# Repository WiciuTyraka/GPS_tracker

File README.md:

# Rocket Localization System

## About

[PUT Rocket Lab](https://tyraka.pl/) jest Kołem Naukowym z Politechniki Poznańskiej zajmującym się projektowaniem, budowaniem oraz testowaniem technologii
rakietowych. Flagowym projektem zespołu jest budowa rakiety sondażowej
Hexa 2 napędzanej hybrydowym silnikiem rakietowym. Jednym z większych problemów, z jakimi przychodzi zmagać się inżynierom budującym
rakiety, jest ich odzysk. Podczas testów rakieta zostaje wystrzelona w
przestrzeń. Wysokość oraz uzyskiwana prędkość obiektu jest oszacowana z
dużą dokładnością. Komplikacje pojawiają się przy estymowaniu miejsca
spadku rakiety, gdyż jest ono zależne w głównej mierze od powodzenia się
wszystkich procedur lądowania oraz w dużym stopniu od czynników meteorologicznych. Istotą odzysku jest zlokalizowanie rakiety w celu znalezienia
części, które są zdatne do ponownego użycia oraz tych, które już nie zadziałają, ale by zanieczyszczały środowisko. Większość zespołów decyduje
się na bardzo drogie komercyjne rozwiązania, które mimo wszystko nie są
wolne od ograniczeń. W tym repozytorium przedstawiony jest autorski projekt systemu lokalizacji rakiet stratosferycznych.

- [Rocket Localization System](#rocket-localization-system)
  - [About](#about)
  - [GPS Tracker](#gps-tracker)
    - [Hardware](#hardware)
      - [Sensors and Components](#sensors-and-components)
      - [Schema](#schema)
      - [Board](#board)
    - [Software](#software)
      - [Block Diagram](#block-diagram)
  - [Receiver](#receiver)
    - [Hardware](#hardware-1)
      - [Sensors and Components](#sensors-and-components-1)
      - [Schema](#schema-1)
      - [Board](#board-1)
    - [Software](#software-1)
      - [Block Diagram](#block-diagram-1)
  - [LoRa Library - RadioTyraka](#lora-library---radiotyraka)
  - [Mobile App](#mobile-app)
    - [Software](#software-1)
  - [App's](#app's)

## GPS Tracker

Pierwszą częścia systemu lokalizacji jest GPS Tracker. Urządzenie to umieszczone wewnątrz rakiety, przy pomocy fal radiowych rozsyła informację na temat swojego aktualnego połorzenia w przestrzeni.

### Hardware

Do komunikacji radiowej ziemia-powietrze posłużyła warstwa fizyczna systemu dalekiego zasięgu - LoRa, protokuł łączności został zaimplementowany według potrzeb naszego zespołu. LoRa używa techniki modulacji z widmem rozproszonym CSS (ang. chirp spread spectrum), która jest uznawana za pierwszą niskokosztową implementację tego rodzaju modulacji do zastosowań komercyjnych. Długość i szerokość geograficzna pozyskiwane są za pomooca systemu nawigacji satelitarnej. Wysokość obliczana jest na podstawie odczytu ciśnienia atmosferycznego mierzonego przez barometr. Z uwagi na stosunkowo niską przepustowość łącza radiowego wszystkie nadmiarowe dane zapisywane sa w trwałej pamięci flash.

Urządzenie jest także wyposażone w akumulator litowo-polimerowy i moduł umożliwiający jego ładowanie przez złącze mini-USB. Cztery diody led pełnią rolę prostego interfejsu, który informuje użytkownika o bierzących ustawieniach. Ustawienia te mogą być konfigurowane poprzez deydkowaną aplikację, która pozwala na ustawienie takich parametrów jak kanał radiowy, moc transmitowanego sygnału oraz data rate. Komunikacja z aplikacją odbywa się poprzez uniwersalny port asynchroniczny - UART. Urządzenie posiada 4 pinowe złącze któe przy pomocy konwertera UART-USB umożliwia podłączenie do komputera. Ostatnim ważnym elementem urządzenia jest włącznik zasilania o logice bistabilnej. Urządzenie zostaje uruchomione poprzez wyciągnięcie specjalnej zworki, tzw "Remove before fly".

<div align="center"><font size="2"><em>Figure 1. Render of GPS Tracker Board</em></font></div>

#### Sensors and components

<details>

Poniższa tabela przedstawia wszytkie moduły cyforwe wykorzystane w projekcie GPS tracker'a wraz z odnośnikiem do poszczególnych dokumentacji.

| Sensor          |          Device |                                                    Datasheet |
| --------------- | --------------: | -----------------------------------------------------------: |
| uC              |      STM32 F411 |              [datasheet](Hardware/datasheet/stm32f411ce.pdf) |
| GPS             |     Quectel L80 | [datasheet](Hardware/datasheet/L80_Hardware_Design_V1.1.pdf) |
| Radio           | LoRa E32-ttl-1W |   [datasheet](Hardware/datasheet/E32-433T30D_Usermanual.pdf) |
| Barometer       |          BMP280 |               [Hardware/datasheet](datasheet/BST-BMP280.pdf) |
| Flash memory    |         W25Q128 |                [Hardware/datasheet](datasheet/w25q128fv.pdf) |
| Battery charger | MCP73833-AMI/UN |             [Hardware/datasheet](datasheet/22005a-76648.pdf) |

</details>

#### Schema

<details>

Poniżej przedstawiony został dokładny schemat GPS tracker'a.

- [link do pliku z schematem](Hardware/gps_tracker2.0/gps_tracker2.0.sch)

<div align="center"><font size="2"><em>Figure 2. Schema of GPS Tracker</em></font></div>

</details>

#### Board

<details>

Na poniższym obrazku przedstawione zostały obie strony dwustronnej płytki PCB, która łączy wszytskie elementy. Lewa strona (niebieskie ścieżki) przedstawia dolną warstwę natomiast prawa (czerwone ścieżki) górną warstwę.

- [link do piku z płytką PCB](Hardware/gps_tracker2.0/gps_tracker2.0.sch)

<div align="center"><font size="2"><em>Figure 3. GPS Tracker board</em></font></div>

</details>

### Software

Napisanie oprogramowania obsługującego moduły urządzenia oraz utworzenie protokołu komunikacyjnego jest niezbędne, by obsłużyć hardware i spełnić wymagania,
które stawiane są przed GPS Tracker'em. W tym celu wykorzystany został popularny framework STM32duino wraz, który jest wygodną i przyjemną platformą do tworzenia aplikacji dla
systemów wbudowanych.
GPS Tracker działa w oparciu o system czasu rzeczywistego FreeRTOS, aby dawać gwarancję wykonania zadań w określonym czasie. Symulacja wielowątkowego działania procesora pozwala
na odczytywanie danych z wszytskich sensorów z maksymalną częstotliwością czujników. Wszystkie dane zapisywane są w trwałej pamięci flash, dzięki czemu po znaleieniu rakiety mogą zostać one odczytane, a na ich podstawie możliwe jest wykreślenie na mapie dokładnego toru lotu rakiety.

Na potrzeby obsługi nowoczesnego modułu komunikacji dalekiego zasięgu -
LoRa - została napisana dedykowana biblioteka. Więcej informacji na jej temat można znaleźć [tutaj](#lora-library---radiotyraka)

#### Block Diagram

<details>

Na pozniższym obrazku przedstawiony został schemat blokowy procesów wykonywanych w ramach działania systemu czasu rzeczywistego zaimplementowanego na potrzeby obługi GPS Tracker'a.

- [link do pliku z kodem źródłowym GPS Tracker'a](Software/gps_tracker/transmiterRTOS_ConfigRadioTyraka.ino)

<div align="center"><font size="2"> <em>Figure 4. GPS Tracker code diagram</em></font></div>

</details>

## Receiver

Drugą częścią systemu jest Receiver, który wraz z smartfonem tworzy stację odbiorczą dla sygnału emitowanego z rakiety. Urządzenie wyposażone w antenę kierunkową pozwala na łączność z rakietami odbywającymi loty stratosferyczne. Odebrane dane wizualizowane są w czasie rzeczywistym na mapie satelitarnej na ekranie połączonego smartfona.

### Hardware

Receiver jest stosunkowo prostym urządzeniem, wyposażoy jest oczywiście w odbiornik radiowy umożliwiający nawiązenie komunikaji radiowej z rakietą oraz jego działanie oparte jest o mikrokontroler ESP32, który posiada zintegrowany moduł Bluetooth i Wi-Fi. Urządzenie wyposażone jest także w 4 złącza umożliwiające komunikację przewodową poprzez różne protokoły, takie jak 2x UART, SPI, I2C. Zastosowanie tak mnogiej liczby interfejsów sprawia, że receiver jest bardzo uniwersalnym urządzeniem, które może zostać w łatwy i przyjemny sposób wykorzystane w wielu projektach jako gateway dla sygnału radiowego LoRa.

Na potrzeby naszego systemu wykorzystywane są trzy interfejsy. Przy pomocy standardu bezprzewodowego Bluetooth Receiver łączy się z smartfonem który przy pomocy dedykowanej aplikacji staje wyświetlaczem dla danych telemetrycznych odbieranych z rakiety.
standard komunikacji Wi-Fi, wykorzystywany jest do postowania odebranych danych na server za pomocą rest api.
Użytkownik ma dostęp do nich poprzez naszą aplikację, która archiwizuje i umożliwia przeglądanie wszystkich danych z różnych lotów i testów.
Ostatnim wykorzystanym interfejsem jest UART, podpobnie jak w przypadku GPS Tracker'a służy on do konfigurowania parametrówtransmisji takich jak kanał radiowy, moc transmitowanego sygnału oraz data rate.

<div align="center"><font size="2"><em>Figure 1. Render of Receiver Board</em></font></div>

#### Sensors and components

<details>

Poniższa tabela przedstawia wszytkie moduły cyforwe wykorzystane w projekcie GPS tracker'a wraz z odnośnikiem do poszczególnych dokumentacji.

| Sensor |          Device |                                                  Datasheet |
| ------ | --------------: | ---------------------------------------------------------: |
| uC     |           ESP32 |        [datasheet](Hardware/datasheet/esp32_datasheet.pdf) |
| Radio  | LoRa E32-ttl-1W | [datasheet](Hardware/datasheet/E32-433T30D_Usermanual.pdf) |

</details>

#### Schema

<details>

Poniżej przedstawiony został dokładny schemat Receivera.

- [link do pliku z schematem](Hardware/receiver/receiver.sch)

<div align="center"><font size="2"><em>Figure 5. Schema of Receiver</em></font></div>

</details>

#### Board

<details>

Na poniższym obrazku przedstawione zostały obie strony dwustronnej płytki PCB, która łączy wszytskie elementy. Lewa strona (niebieskie ścieżki) przedstawia dolną warstwę natomiast prawa (czerwone ścieżki) górną warstwę.

- [link do piku z płytką PCB](Hardware/receiver/receiver.brd)

<div align="center"><font size="2"><em>Figure 6. Receiver board</em></font></div>

</details>

### Software

Podobnie jak w przypadku GPS Tracker'a kod został napisany z wykorzystaniem freamworku Arduino. Jednak w tym przypadku system czasu rzeczywistego nie został wykorzystany, kod działa w sposób proceduralny.
Do obsługi modułu komunikacji radiowej, również została wykorzystana autorska biblioteka.

#### Block Diagram

<details>

Na pozniższym obrazku przedstawiony został schemat blokowy proceduralnego kodu Receiver'a

- [link do pliku z kodem źródłowym Receiver'a](Software/receiver/eciverRadioTyrakaV2.ino)

<div align="center"><font size="2"> <em>Figure 7. Receiver code diagram</em></font></div>

</details>

## LoRa Library - RadioTyraka

Na potrzeby obsługi nowoczesnego modułu komunikacji dalekiego zasięgu -
LoRa - została napisana dedykowana biblioteka. Biblioteka implementuje protokuł komunkacyjny, który znacząco ułatwia komunikację radiową natomiast obsługa modułu jest przyjamna dla użytkownika. Wydajność łącza radiowego uzyskana dzięki oprogramowaniu naszego zespołu jest większa niż w przypadku użytkowania biblioteki afirmowanej przez producenta modułu.

RadioTyraka powstało jako nakładka na popularną bibliotekę [RadioHead](https://www.airspayce.com/mikem/arduino/RadioHead/). Znacząco usprawnia ona niektóre z funkcji oferowanych przez bibliotekę, a także wprowadza nowe użyteczne rozwiązania. Biblioteka RadioTyraka znajduje się na osobnym repozytorium, które zawiera jej szczegółową dokumentację.

- [link do repozytorium z biblioteką](https://github.com/WiciuTyraka/RadioTyraka)

## Mobile App

W celu wizualizacji lokalizacji szukanego obiektu stworzona została aplikacja mobilna. Aplikacja łączy się za pomocą technologii Bluetooth ze
stacją odbiorczą i pobiera dane dotyczące aktualnej lokalizacji rakiety w czasie rzeczywistym. Dane wizualizowane są na mapie satelitarnej, co
znacznie przyspiesza i ułatwia proces odzyskiwania rakiety.

W celu poprawnego skonfigurowania Receivera ze smartphonem należy w ustawieniach bluetooth telefonu wyszukać i połączyć się z stacją odbiorczą.
Następnie w menu ustawień aplikacji (rys. 8) należy wybrać opcję **connect to paired device**.
W nowym oknie (rys. 9) z sparowanymi urządzeniami, należy wybrać odpowiednie urządzenie i wybrać **select**.
Dzięki temu przejdziemy do głównego okna (rys. 10) z widokiem mapy satelitarnej.

|                                              |                                                |
| :------------------------------------------: | :--------------------------------------------: |
|  |  |

 <div align="center"><font size="2"><em>Figure 8. Mobile app setting </em></font> &nbsp;&nbsp;&nbsp;&nbsp;&nbsp;&nbsp;&nbsp;&nbsp;&nbsp;&nbsp;&nbsp;&nbsp;&nbsp;&nbsp;&nbsp;&nbsp;&nbsp;&nbsp;&nbsp;&nbsp;&nbsp;&nbsp;&nbsp;&nbsp;&nbsp;&nbsp;&nbsp;&nbsp;&nbsp;&nbsp;&nbsp;&nbsp;&nbsp;&nbsp;&nbsp;&nbsp; <font size="2"><em>Figure 9. Mobile app setting 2 </em></font></div>

&nbsp;

Czerwonym znacznikiem oznaczony jest lokalizowany obiket - lokalizacja trckera.
Po kliknięciu na znacznik użytkownik zostanie przeniesiony do map google na których zaznaczona będzie najkrótsza trasa od użytkownika do poszukiwanego obiektu.
w lewym górnym rogu wyświetlany jest czas od ostatniej otrzymanej wiadomośći.

&nbsp;

<div align="center"></div>

<div align="center"><font size="2"><em>Figure 10.  Mobile app satelite map display </em></font></div>

## APP's

Niniejsza praca dyplomowa została zrealizowana wraz z awioniką Tyraka w ramach przedmiotu "Zespołowy projekt inżynierski" na Wydziale Informatyki i Matematyki Uniwersytetu im. Adama Mickiewicza w Poznaniu. Produkty projektu przeznaczone są dla koła rakietowego Politechniki Poznańskiej. Jest to aplikacja, która pozwala na uporządkowanie, analizę, przechowywanie i wyświetlanie danych z testów rakiet oraz silników. Dzięki temu mamy podgląd do danych z czujników na żywo podczas testów, dane są przedstawiane w postaci wykresów oraz mapy z lokalizacją rakiety co ułatwia odczyt danych. Trzeba zadbać o to, by dane były poprawnie zapisane, aby po teście móc wykonać analizę — w tym celu dane będą eksportowe do Excela. W przypadku testu silnika aplikacja oblicza średni ciąg, czas spalania, impuls całkowity oraz właściwy. Testy będą sortowane oraz filtrowane, aby ułatwić do nich dostęp. Aplikacja umożliwia konfigurowanie oraz kontrolowanie modułów elektronicznych, zmianę parametrów uruchomieniowych modułu, odczyt danych i czyszczenie pamięci flash.

Desktopowa aplikacja serwerowa odpowiada za odczytywanie danych wysyłanych przez elektronikę naziemną oraz przekazywanie ich w czasie rzeczywistym do aplikacji desktopowej. Zapisuje też ona otrzymane pomiary do odpowiednich plików JSON, w celu późniejszego wysłania ich do aplikacji webowej.

Serwer lokalny umożliwia również komunikację poprzez interfejs USB z komaptybilnym urządzeniem takim jak GPS tracker lub Receiver. Dzięki temu użytkownik jest w stanie wysyłać do niej polecenia i ma możliwość jej prostej konfiguracji, bez znajomości języka C++. Użytkownik ma też możliwość pobierania i czytania plików bezpośrednio z płytki urządzenia.

Głównym zadaniem webowej aplikacji serwerowej jest gromadzenie i możliwość eksportu danych historycznych do formatu JSON oraz CSV. Każdy użytkownik ma możliwość zalogowania się i dostęp do ograniczonych funkcjonalności aplikacji. Pełen dostęp posiada administrator, który zakłada konta użytkowników i zarządza aplikacją. Serwer webowy korzysta z nierelacyjnej bazy danych. Użytkownicy mają możliwość wyszukiwania konkretnych testów, jak i listowania większej ich ilości za pomocą dostępnych filtrów i funkcji sortujących.

Częścią projektu jest też strona internetowa, która ma pełnić funkcję wizytówki koła w Internecie. Na tej samej domenie co wizytówka będzie można zalogować się jako członek koła i uzyskać dostęp do panelu historii testów. Możliwa będzie analiza i odtworzenie zapisu live z przeprowadzonych testów. Oprócz ich wyświetlania będzie można wgrywać nowe testy z plików oraz eksportować je w formacie JSON i CSV. Kolejną częścią systemu Tyraka jest aplikacja desktopowa stworzona za pomocą frameworka Electron, na której zobaczyć będzie można testy w czasie rzeczywistym, wgrywać testy z plików oraz konfigurować elektronikę. Aplikacja webowa oraz desktopowa napisana jest za pomocą frameworka Vue.js.

<div align="center"><font size="2"><em>Figure 11. config application for GPS tracker </em></font></div>

&nbsp;

&nbsp;

<div align="center"><font size="2"><em>Figure 12. config application for Receiver </em></font></div>

&nbsp;

---

&nbsp;

_by Wiktor Tasarek_

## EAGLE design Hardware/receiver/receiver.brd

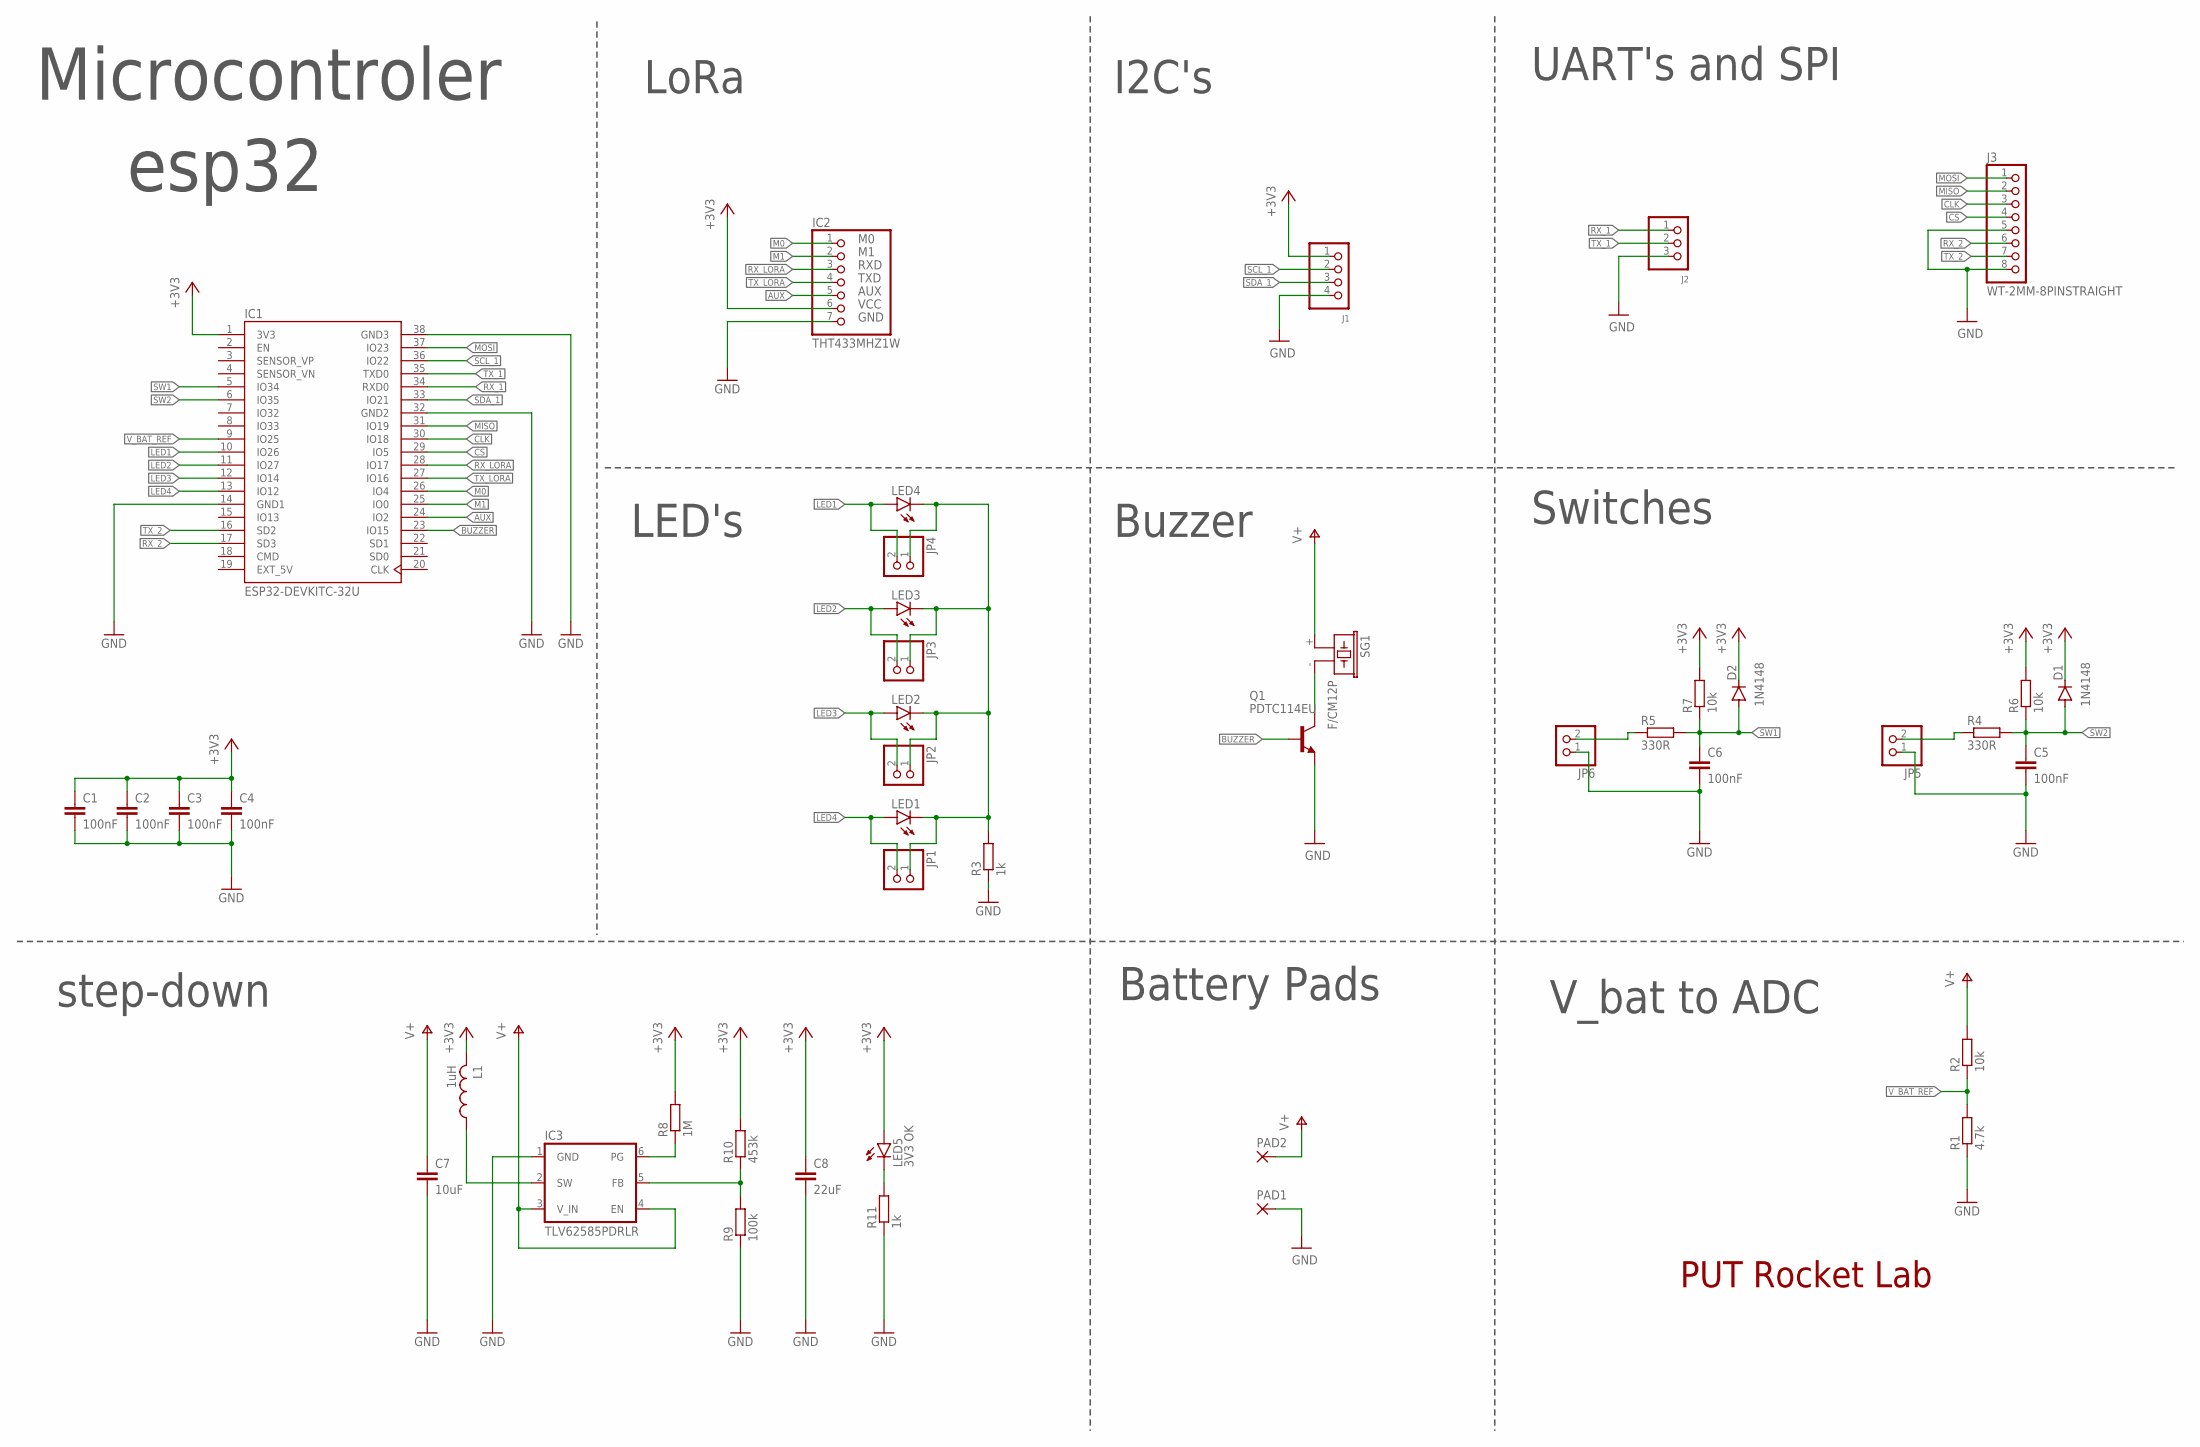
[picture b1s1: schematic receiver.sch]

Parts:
C1, C2, C3, C4, C5, C6: 100nF; C0805
C7: 10uF; C0805
C8: 22uF; C0805
D1, D2: 1N4148; SOD80C
IC1: ESP32-DEVKITC-32U; MODULE_ESP32-DEVKITC-32U
IC2: THT433MHZ1W; E32M1000
IC3: TLV62585PDRLR; SOT563
J1: WT-2MM-4PINSTRAIGHT; W_TYPE_2MM_4_N
J2: WT-2MM-3PINSTRAIGHT; W_TYPE_2MM_3_N
J3: WT-2MM-8PINSTRAIGHT; W_TYPE_2MM_8_N
JP1, JP2, JP3, JP4, JP5, JP6: PINHD-1X2; 1X02
L1: 1uH; L5650M
LED1, LED2, LED3, LED4: LEDCHIPLED_0805; CHIPLED_0805
LED5: 3V3 OK; CHIPLED_0805
PAD1, PAD2: WIREPAD2,54/1,1; 2,54/1,1
Q1: PDTC114EU; SOT23
R1: 4.7k; R0805
R2, R6, R7: 10k; R0805
R3, R11: 1k; R0805
R4, R5: 330R; R0805
R8: 1M; R0805
R9: 100k; R0805
R10: 453k; R0805
SG1: F/CM12P

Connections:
+3V3: C1.1, C2.1, C3.1, C4.1, C8.1, D1.C, D2.C, IC1.1 (3V3), IC2.6 (VCC), J1.1, L1.2, LED5.A, R6.2, R7.2, R8.2, R10.2
AUX: IC1.24 (IO2), IC2.5 (AUX)
BUZZER: IC1.23 (IO15), Q1.1 (B)
CLK: IC1.30 (IO18), J3.3
CS: IC1.29 (IO5), J3.4
EXT_5V: IC1.19 (EXT_5V)
GND: C1.2, C2.2, C3.2, C4.2, C5.2, C6.2, C7.2, C8.2, IC1.14 (GND1), IC1.32 (GND2), IC1.38 (GND3), IC2.7 (GND), IC3.1 (GND), J1.4, J2.3, J3.5, J3.8, JP5.1, JP6.1, PAD1.1, Q1.2 (E), R1.1, R3.1, R9.1, R11.1
LED1: IC1.10 (IO26), JP4.2, LED4.A
LED2: IC1.11 (IO27), JP3.2, LED3.A
LED3: IC1.12 (IO14), JP2.2, LED2.A
LED4: IC1.13 (IO12), JP1.2, LED1.A
M0: IC1.26 (IO4), IC2.1 (M0)
M1: IC1.25 (IO0), IC2.2 (M1)
MISO: IC1.31 (IO19), J3.2
MOSI: IC1.37 (IO23), J3.1
unnamed: JP1.1, JP2.1, JP3.1, JP4.1, LED1.C, LED2.C, LED3.C, LED4.C, R3.2
unnamed: LED5.C, R11.2
unnamed: IC3.5 (FB), R9.2, R10.1
unnamed: IC3.6 (PG), R8.1
unnamed: IC3.2 (SW), L1.1
unnamed: Q1.3 (C), SG1.- (2)
unnamed: JP6.2, R5.1
unnamed: JP5.2, R4.1
RX_1: IC1.34 (RXD0), J2.1
RX_2: IC1.17 (SD3), J3.6
RX_LORA: IC1.28 (IO17), IC2.3 (RXD)
SCL_1: IC1.36 (IO22), J1.2
SDA_1: IC1.33 (IO21), J1.3
SW1: C6.1, D2.A, IC1.5 (IO34), R5.2, R7.1
SW2: C5.1, D1.A, IC1.6 (IO35), R4.2, R6.1
TX_1: IC1.35 (TXD0), J2.2
TX_2: IC1.16 (SD2), J3.7
TX_LORA: IC1.27 (IO16), IC2.4 (TXD)
V+: C7.1, IC3.3 (V_IN), IC3.4 (EN), PAD2.1, R2.2, SG1.+ (1)
V_BAT_REF: IC1.9 (IO25), R1.2, R2.1

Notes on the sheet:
Microcontroler
esp32
LoRa
step-down
LED's
I2C's
UART's and SPI
Buzzer
Battery Pads
V_bat to ADC
Switches
PUT Rocket Lab

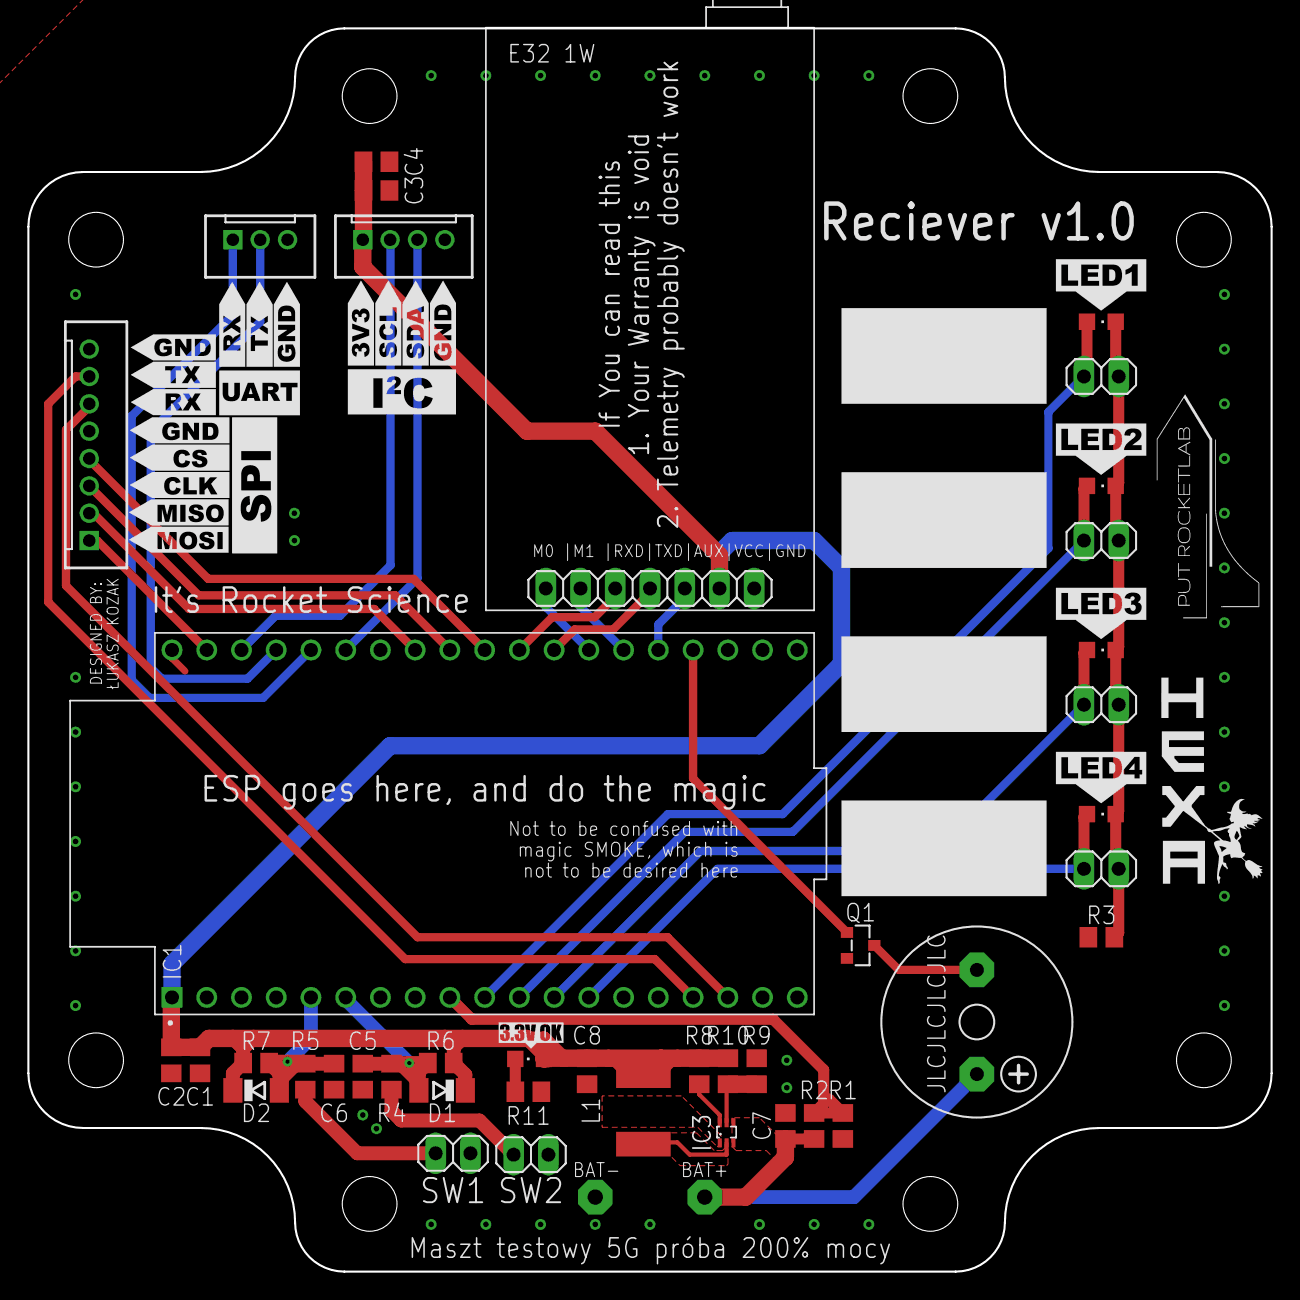
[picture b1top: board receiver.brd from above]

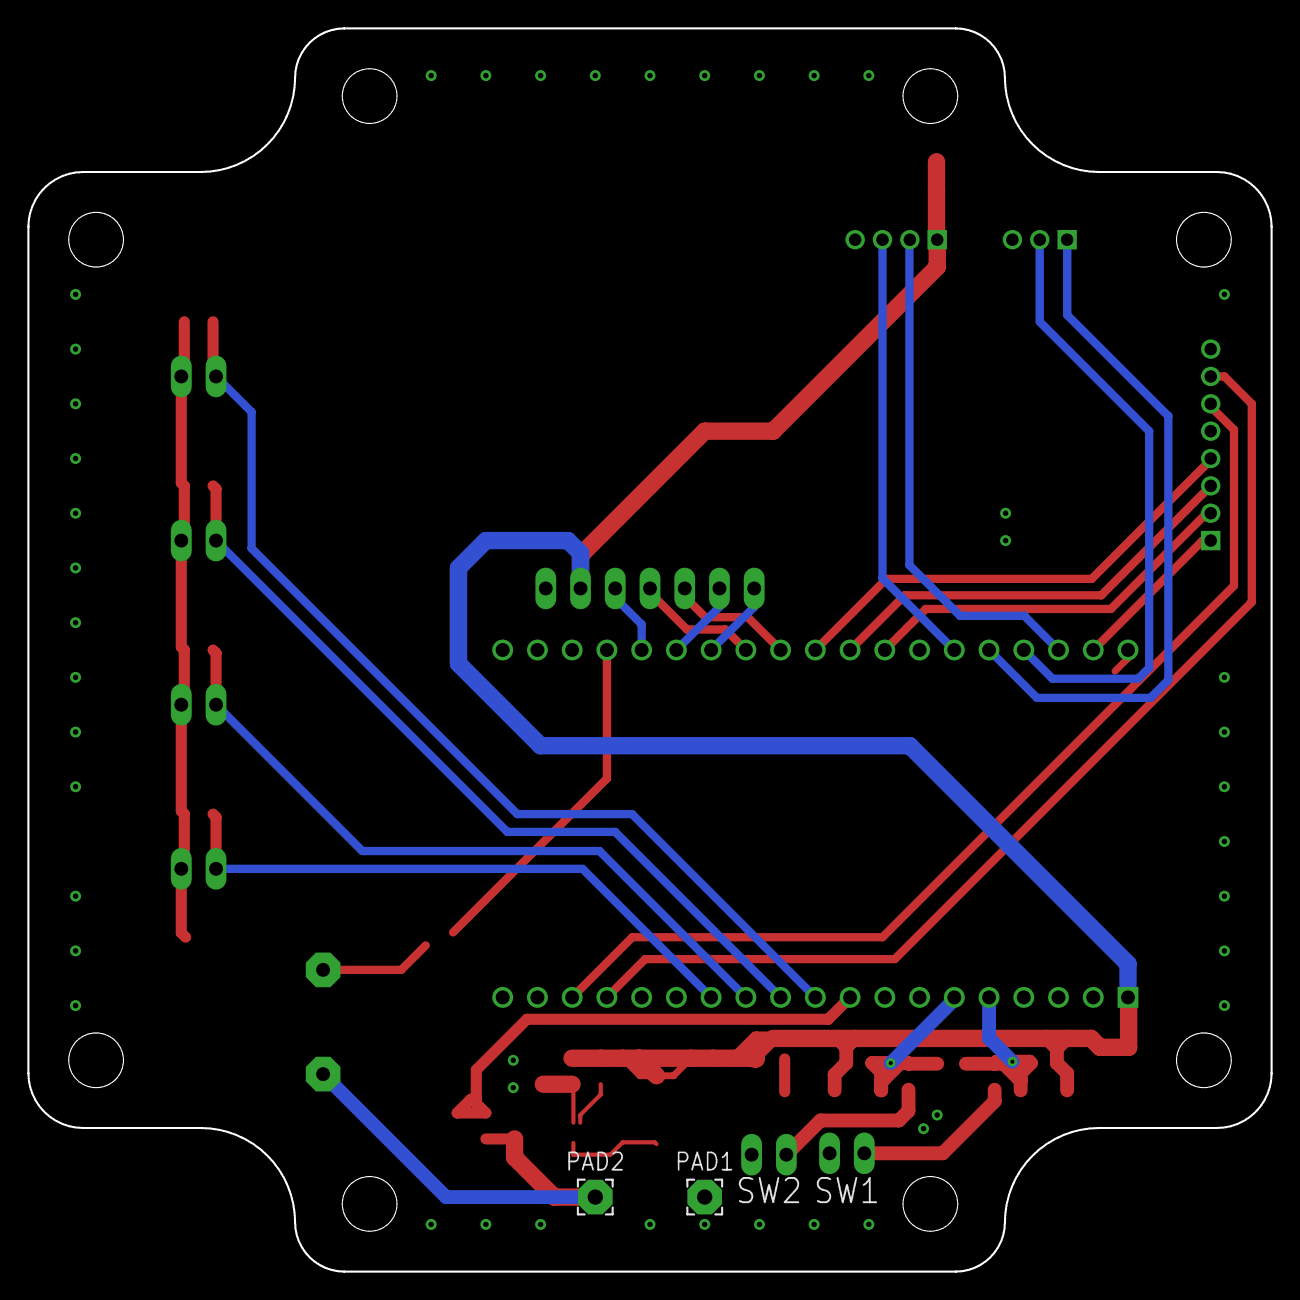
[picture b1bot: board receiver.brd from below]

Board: 2 copper layers, 90.9 x 90.9 mm, 43 parts (2 on the bottom side), 34 nets.

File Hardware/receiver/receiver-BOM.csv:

Qty;Value;Device;Package;Parts;Comment;Description
6;100nF;C-EUC0805;C0805;C1, C2, C3, C4, C5, C6;;CAPACITOR, European symbol
1;10uF;C-EUC0805;C0805;C7;;CAPACITOR, European symbol
1;22uF;C-EUC0805;C0805;C8;;CAPACITOR, European symbol
2;1N4148;DIODE-SOD80C;SOD80C;D1, D2;;DIODE
1;ESP32-DEVKITC-32U;ESP32-DEVKITC-32U;MODULE_ESP32-DEVKITC-32U;IC1;;ESP32-DEVKITC Check prices
1;THT433MHZ1W;THT433MHZ1W;E32M1000;IC2;;
1;TLV62585PDRLR;TLV62585PDRLR;SOT563;IC3;;
1;1uH;L-USL5650M;L5650M;L1;;INDUCTOR, American symbol
4;;LEDCHIPLED_0805;CHIPLED_0805;LED1, LED2, LED3, LED4;Blue;LED
1;3V3 OK;LEDCHIPLED_0805;CHIPLED_0805;LED5;Red;LED
1;PDTC114EU;BC846ASMD;SOT23;Q1;;NPN Transistor
1;4.7k;R-EU_R0805;R0805;R1;;RESISTOR, European symbol
1;453k;R-EU_R0805;R0805;R10;;RESISTOR, European symbol
3;10k;R-EU_R0805;R0805;R2, R6, R7;;RESISTOR, European symbol
2;1k;R-EU_R0805;R0805;R3, R11;;RESISTOR, European symbol
2;330R;R-EU_R0805;R0805;R4, R5;;RESISTOR, European symbol
1;1M;R-EU_R0805;R0805;R8;;RESISTOR, European symbol
1;100k;R-EU_R0805;R0805;R9;;RESISTOR, European symbol
1;F/CM12P;F/CM12P;F/CM12P;SG1;;BUZZER Source: Buerklin

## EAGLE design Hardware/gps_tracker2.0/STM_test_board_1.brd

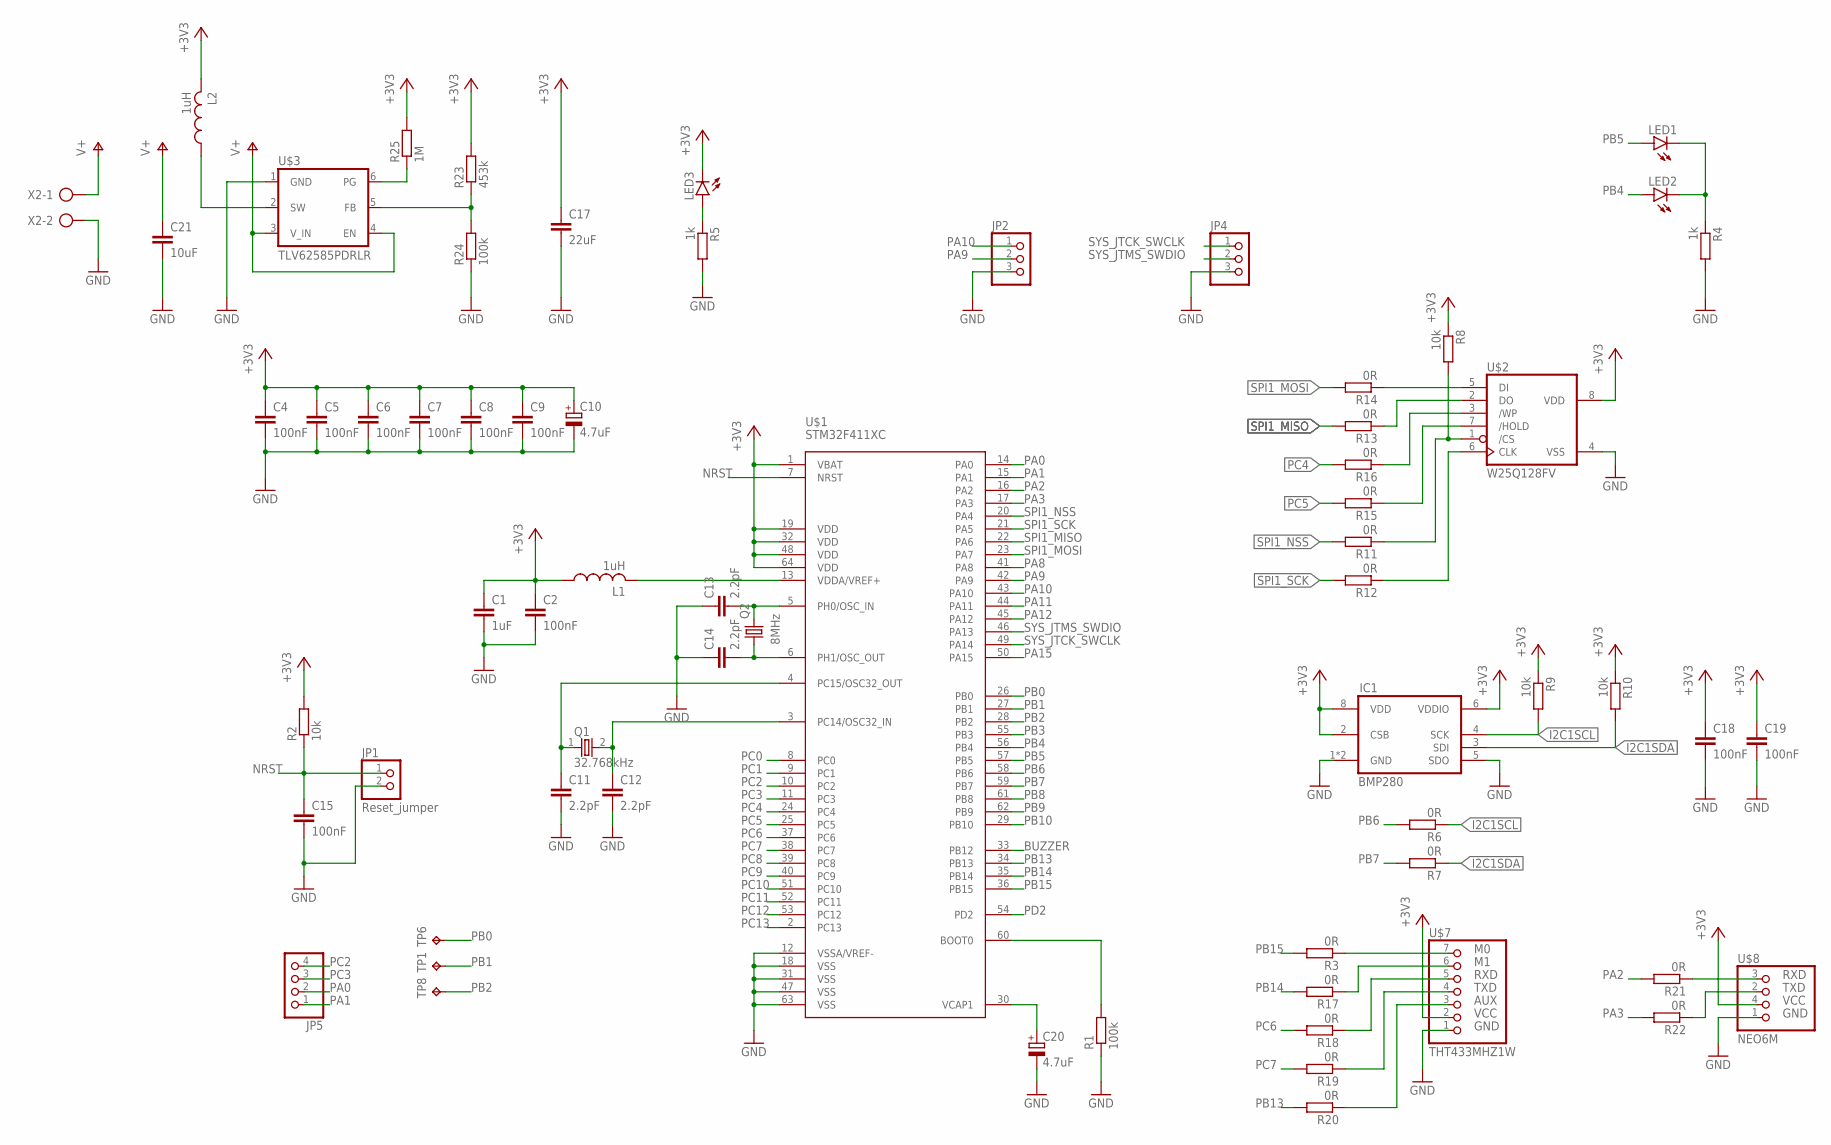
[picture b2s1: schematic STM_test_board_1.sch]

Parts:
C1: 1uF; C1206
C2, C4, C5, C6, C7, C8, C9, C15, C18, C19: 100nF; C0805
C10, C20: 4.7uF; CT3216
C11, C12, C13, C14: 2.2pF; C0805
C17: 22uF; C1206
C21: 10uF; C0805
IC1: BMP280
JP1: Reset_jumper; 1X02
JP2, JP4: PINHD-1X3M; 1X03M
JP5: PINHD-1X4M; 1X04M
L1: 1uH; 0207/7
L2: 1uH; L5650M
LED1, LED2, LED3: LEDSMT1206; 1206
Q1: 32.768kHz; MA507
Q2: 8MHz; CTS406
R1, R24: 100k; R0805
R2, R8, R9, R10: 10k; R0805
R3, R6, R7, R11, R12, R13, R14, R15, R16, R17, R18, R19, R20, R21, R22: 0R; R0805
R4, R5: 1k; R0805
R23: 453k; R1206
R25: 1M; R1206
TP1, TP6, TP8: TPTP20SQ; TP20SQ
U$1: STM32F411XC; LQFP64
U$2: W25Q128FV; TSSOP-8
U$3: TLV62585PDRLR; SOT563
U$7: THT433MHZ1W; E32M1000
U$8: NEO6M; 1X04
X2: AK300/2

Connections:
+3V3: C1.1, C2.1, C4.1, C5.1, C6.1, C7.1, C8.1, C9.1, C10.+, C17.1, C18.1, C19.1, IC1.2 (CSB), IC1.6 (VDDIO), IC1.8 (VDD), L1.1, L2.2, LED3.C, R2.2, R8.1, R9.1, R10.1, R23.2, R25.2, U$1.1 (VBAT), U$1.19 (VDD), U$1.32 (VDD), U$1.48 (VDD), U$1.64 (VDD), U$2.8 (VDD), U$7.2 (VCC), U$8.4 (VCC)
BUZZER: U$1.33 (PB12)
GND: C1.2, C2.2, C4.2, C5.2, C6.2, C7.2, C8.2, C9.2, C10.-, C11.2, C12.2, C13.1, C14.1, C15.2, C17.2, C18.2, C19.2, C20.-, C21.2, IC1.1 (GND), IC1.5 (SDO), IC1.7 (GND), JP1.2, JP2.3, JP4.3, R1.1, R4.2, R5.2, R24.1, U$1.12 (VSSA/VREF-), U$1.18 (VSS), U$1.31 (VSS), U$1.47 (VSS), U$1.63 (VSS), U$2.4 (VSS), U$3.1 (GND), U$7.1 (GND), U$8.1 (GND), X2.2
I2C1SCL: IC1.4 (SCK), R6.1, R9.2
I2C1SDA: IC1.3 (SDI), R7.1, R10.2
unnamed: C13.2, Q2.3 (2), U$1.5 (PH0/OSC_IN)
unnamed: C20.+, U$1.30 (VCAP1)
unnamed: C12.1, Q1.2, U$1.3 (PC14/OSC32_IN)
unnamed: C11.1, Q1.1, U$1.4 (PC15/OSC32_OUT)
unnamed: C14.2, Q2.1, U$1.6 (PH1/OSC_OUT)
unnamed: R1.2, U$1.60 (BOOT0)
unnamed: L1.2, U$1.13 (VDDA/VREF+)
unnamed: R14.1, U$2.5 (DI)
unnamed: R13.1, U$2.2 (DO)
unnamed: R12.1, U$2.6 (CLK)
unnamed: R16.1, U$2.3 (/WP)
unnamed: R15.1, U$2.7 (/HOLD)
unnamed: R3.1, U$7.7 (M0)
unnamed: R8.2, R11.1, U$2.1 (/CS)
unnamed: R17.1, U$7.6 (M1)
unnamed: R18.1, U$7.5 (RXD)
unnamed: R19.1, U$7.4 (TXD)
unnamed: R20.1, U$7.3 (AUX)
unnamed: R21.1, U$8.3 (RXD)
unnamed: LED1.C, LED2.C, R4.1
unnamed: LED3.A, R5.1
unnamed: R22.1, U$8.2 (TXD)
unnamed: R23.1, R24.2, U$3.5 (FB)
unnamed: R25.1, U$3.6 (PG)
unnamed: L2.1, U$3.2 (SW)
NRST: C15.1, JP1.1, R2.1, U$1.7 (NRST)
PA0: JP5.2, U$1.14 (PA0)
PA1: JP5.1, U$1.15 (PA1)
PA2: R21.2, U$1.16 (PA2)
PA3: R22.2, U$1.17 (PA3)
PA8: U$1.41 (PA8)
PA9: JP2.2, U$1.42 (PA9)
PA10: JP2.1, U$1.43 (PA10)
PA11: U$1.44 (PA11)
PA12: U$1.45 (PA12)
PA15: U$1.50 (PA15)
PB0: TP6.TP, U$1.26 (PB0)
PB1: TP1.TP, U$1.27 (PB1)
PB2: TP8.TP, U$1.28 (PB2)
PB3: U$1.55 (PB3)
PB4: LED2.A, U$1.56 (PB4)
PB5: LED1.A, U$1.57 (PB5)
PB6: R6.2, U$1.58 (PB6)
PB7: R7.2, U$1.59 (PB7)
PB8: U$1.61 (PB8)
PB9: U$1.62 (PB9)
PB10: U$1.29 (PB10)
PB13: R20.2, U$1.34 (PB13)
PB14: R17.2, U$1.35 (PB14)
PB15: R3.2, U$1.36 (PB15)
PC0: U$1.8 (PC0)
PC1: U$1.9 (PC1)
PC2: JP5.4, U$1.10 (PC2)
PC3: JP5.3, U$1.11 (PC3)
PC4: R16.2, U$1.24 (PC4)
PC5: R15.2, U$1.25 (PC5)
PC6: R18.2, U$1.37 (PC6)
PC7: R19.2, U$1.38 (PC7)
PC8: U$1.39 (PC8)
PC9: U$1.40 (PC9)
PC10: U$1.51 (PC10)
PC11: U$1.52 (PC11)
PC12: U$1.53 (PC12)
PC13: U$1.2 (PC13)
PD2: U$1.54 (PD2)
SPI1_MISO: R13.2, U$1.22 (PA6)
SPI1_MOSI: R14.2, U$1.23 (PA7)
SPI1_NSS: R11.2, U$1.20 (PA4)
SPI1_SCK: R12.2, U$1.21 (PA5)
SYS_JTCK_SWCLK: JP4.1, U$1.49 (PA14)
SYS_JTMS_SWDIO: JP4.2, U$1.46 (PA13)
V+: C21.1, U$3.3 (V_IN), U$3.4 (EN), X2.1

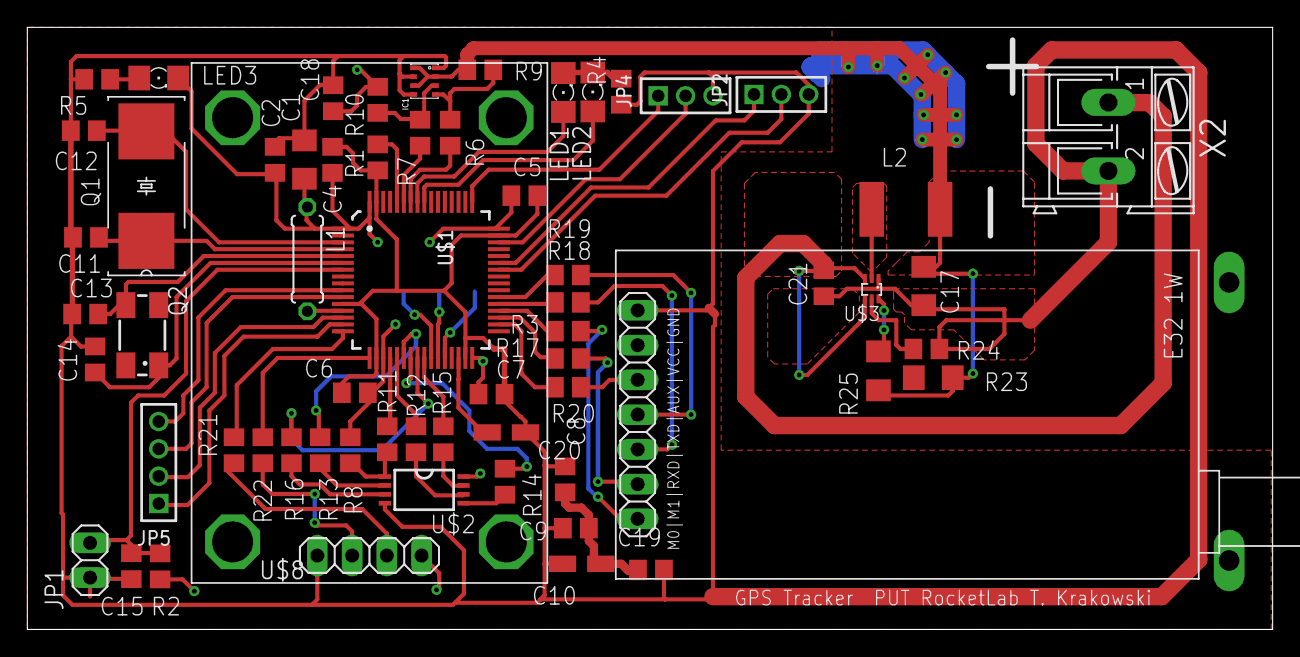
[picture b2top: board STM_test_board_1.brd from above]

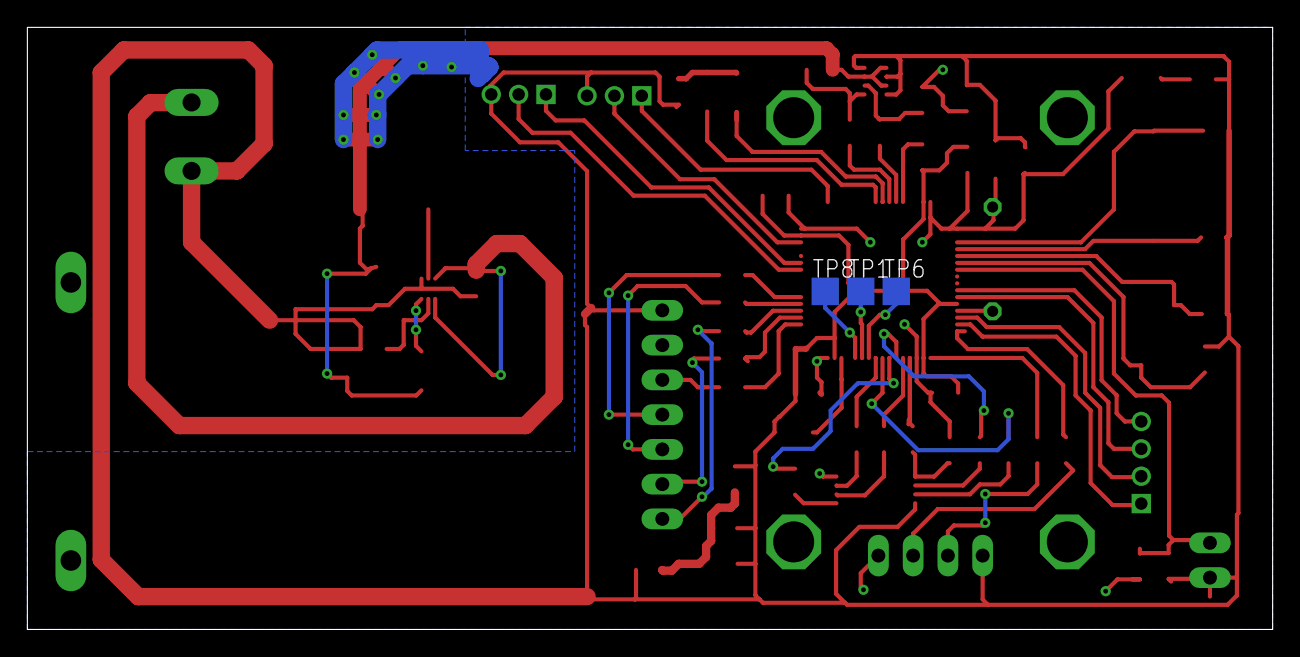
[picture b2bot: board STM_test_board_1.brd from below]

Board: 2 copper layers, 91.0 x 44.0 mm, 65 parts (3 on the bottom side), 59 nets.

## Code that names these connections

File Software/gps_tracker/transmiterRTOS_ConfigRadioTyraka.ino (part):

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#include <Adafruit_BMP280.h>

//Define configuration interupt
#define configInterupt PB15

//Define led pins
#define led1 PB0  //error
#define led2 PB1  // setup done
#define led3 PB2  // lora init done
#define led4 PB10 // flesh write

// Define lora pins
#define tx PA9
#define rx PA10
#define m0 PA11
#define m1 PA12
#define aux PC13

// define flash pins:
#define flashCs PA8
//#define flashMiso PA6
//#define flashMosi PA7
//#define flashWp PC4
//#define flashHold PA4
//#define clk PA5

// define bmp280 pins
#define sda PB7
#define scl PB6

// inicialize queue for BMP Task
QueueHandle_t xQueue_Pressure;
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QueueHandle_t xQueue_Logger;

// Define Hardware Serials:
HardwareSerial logSerial(PC7, PC6); // RX, TX
// Logger logger(&logSerial);                 // Logger inicialization
FlashSPI flash(&logSerial); // Flash inicialization
//-----------------------------------------------------------------------------------
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    //---------------------------------------------------------------------------

    //  Inicialize pinMode for leds
    pinMode(led1, OUTPUT);
    //    logger.info(F("setup"), "led1 - error set to pin " + String(led1, DEC));
    pinMode(led2, OUTPUT);
    //    logger.info(F("setup"), "led2 - setup done set to pin " + String(led2, DEC));
    pinMode(led3, OUTPUT);
    //    logger.info(F("setup"), "led3 - init success set to pin " + String(led3, DEC));
    pinMode(led4, OUTPUT);
    //    logger.info(F("setup"), "led4 - flesh write set to pin " + String(led4, DEC));
    //---------------------------------------------------------------------------

    // Begin BMP280 I2C
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
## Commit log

2021-01-14 short description
    short description
2021-01-14 schema_pic
    schema_pic
2021-01-14 pic descriptions
    pictures descriptions
2021-01-14 pic change
    pic change
2021-01-14 main description change
    main description change
2021-01-14 board
    gps tracker board
2021-01-14 software
    software
2021-01-14 receiver
    receiver
2021-01-16 receviver
    receiver
2021-01-18 eceiver upadate
    receiver update
2021-01-18 "/" slash
    slash
2021-01-23 lora-lib
    lora-lib
2021-01-24 library desc
    library desc
2021-01-24 fix
    fix
